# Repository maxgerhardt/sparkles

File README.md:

# Project sketch: whispering forest fireflies

### Motivation: 
Forests are amazing to illuminate but unfortunately most lighting art i have seen in the past years are immediately recognizable as LED strips. Also i’m looking for a technical challenge.

### Short description: 
build autonomous little waterproof devices that can be hung up in trees. They blink and have a speaker and can triangulate their relative position to each other by using sound. This way we can simply hang them up randomly and know where they are, running light and sound animations through a larger space. 

### How does this work? 
One base station knows its exact location and sends out a timestamp every second or so. During calibration we walk around the forest and produce loud noises, each individual device picks up those noises as peaks and calculates the time difference between the timestamp and the peak, thus collecting a table of runtimes. These runtimes are then sent to the base station and this way we can calculate each position with an accuracy of at least 30cm (which would be 1ms granularity for sound in air) or even quicker. We use ESP-NOW as wifi broadcast for the timestamp and additional commands. 

### How does the hardware look like? 
It’s going to be a custom pcb with a high power led on each side, an esp32, a cheap SMD microphone, a switch and some charging infrastructure, plus a loud speaker  You can plug in a lithium polymer battery and an esp8266 dev board to the pin headers. The whole thing needs to be encased in something waterproof but the idea is to smartly use the ESPs sleep functions to keep the whole thing running for the entire week and only work at night. 

### How do you want to charge 200 devices? 
Actually, we hope to get the battery and power consumption set up in a way that the devices can run for a whole week (power down during daylight etc), but the idea is also to have two notches in the width of a model railway track on the PCBs, so we can stick the boards on a long piece of track and charge all of them more or less at once. We might also do a sound installation during daytime and a light installation at night which creates even bigger need for charging infrastructure

### What challenges are there? 
Many. Getting the math of the audio triangulation right, actually doing some audio triangulation, getting an energy saving way of doing the wifi command stuff, possibly doing our own PWM on the LEDs instead of using WS2812 (e.g. to use brighter LEDs), getting some nice anmations running, also getting the sound animation right, getting all of this done in a cheap fashion etc etc. 

### Costs? 
The cheaper the unit the more we can make. I hope to get a unit including battery for under 10 euros and i hope to get a dream funded that allows us to get 200 units. The cool thing is that every year we could increase the amount of units to make the thing even more sparkly…

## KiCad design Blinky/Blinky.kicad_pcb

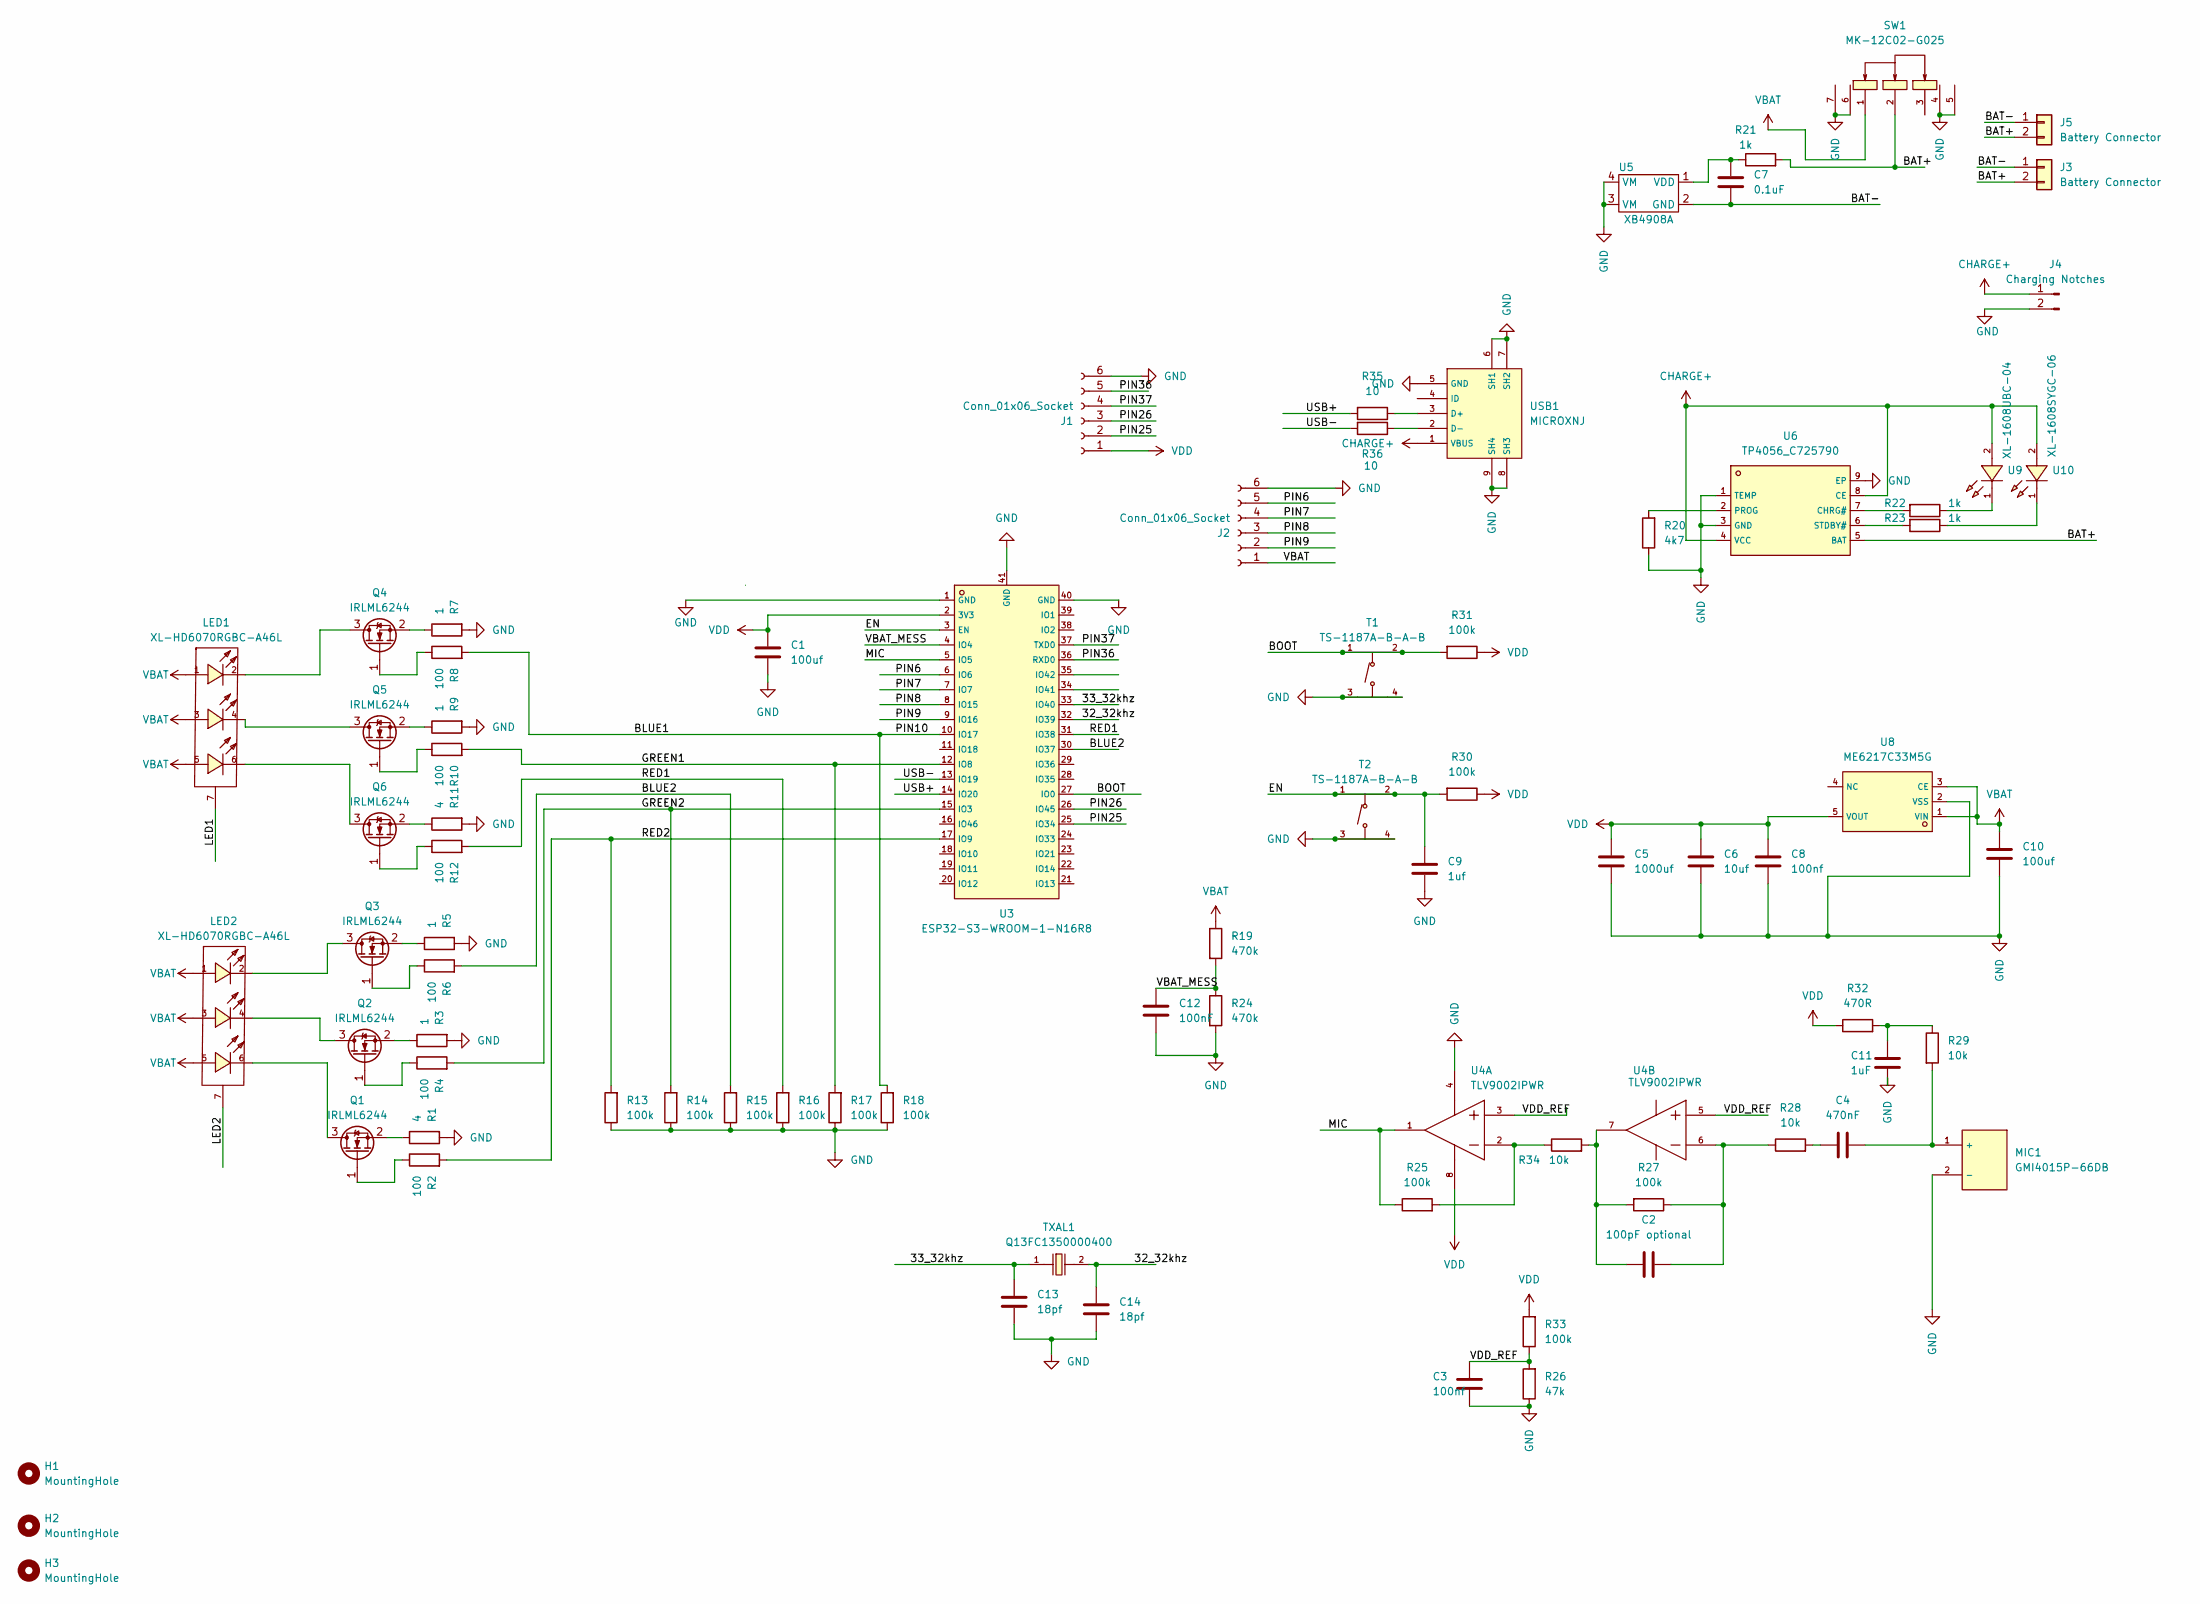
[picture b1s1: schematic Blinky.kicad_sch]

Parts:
C1, C10: 100uf; CASE-B_3528
C2: 100pF optional; C_0603_1608Metric
C3, C8: 100nf; C_0603_1608Metric
C4: 470nF; C_0603_1608Metric
C5: 1000uf; CAP-SMD_BD8.0-L8.3-W8.3-FD
C6: 10uf; C_0603_1608Metric
C7: 0.1uF; C_0603_1608Metric
C9: 1uf; C_0603_1608Metric
C11: 1uF; C_0603_1608Metric
C12: 100nF; C_0603_1608Metric
C13, C14: 18pf; C_0603_1608Metric
H1, H2, H3: MountingHole; MountingHole_3.2mm_M3
J1, J2: Conn_01x06_Socket; HDR-TH_6P-P2.54-V-F
J3, J5: Battery Connector; JST_PH_B2B-PH-K_1x02_P2.00mm_Vertical
J4: Charging Notches; ChargingNotches
LED1, LED2: XL-HD6070RGBC-A46L; LED-SMD_XL-HD6070RGBC-A46L; LCSC C5349977
MIC1: GMI4015P-66DB; MIC-TH_BD4.0-P1.4-D0.4-L-FD; LCSC C529912
Q1, Q2, Q3, Q4, Q5, Q6: IRLML6244; SOT-23
R1, R11: 4; R_0603_1608Metric
R2, R4, R6, R8, R10, R12: 100; R_0603_1608Metric
R3, R5, R7, R9: 1; R_0603_1608Metric
R13, R14, R15, R16, R17, R18, R25, R27, R30, R31, R33: 100k; R_0603_1608Metric
R19, R24: 470k; R_0603_1608Metric
R20: 4k7; R_0603_1608Metric
R21, R22, R23: 1k; R_0603_1608Metric
R26: 47k; R_0603_1608Metric
R28, R29, R34: 10k; R_0603_1608Metric
R32: 470R; R_0603_1608Metric
R35, R36: 10; R_0603_1608Metric
SW1: MK-12C02-G025; SW-SMD_MK-12C02-G025; LCSC C778186
T1, T2: TS-1187A-B-A-B; SW-SMD_4P-L5.1-W5.1-P3.70-LS6.5-TL-2; LCSC C318884
TXAL1: Q13FC1350000400; Crystal_SMD_3215-2Pin_3.2x1.5mm; LCSC C32346
U3: ESP32-S3-WROOM-1-N16R8; WIRELM-SMD_ESP32-S3-WROOM-1; LCSC C3040594
U4: TLV9002IPWR; TSSOP-8_L4.4-W3.0-P0.65-LS6.4-BL-2; LCSC C398359
U5: XB4908A
U6: TP4056_C725790; ESOP-8_L4.9-W3.9-P1.27-LS6.0-BL-EP; LCSC C725790
U8: ME6217C33M5G; SOT-23-5_L3.0-W1.7-P0.95-LS2.8-BR; LCSC C427602
U9: XL-1608UBC-04; LED0603-RD_BLUE; LCSC C965807
U10: XL-1608SYGC-06; LED0603-RD_GREEN; LCSC C965805
USB1: MICROXNJ; MICRO-USB-SMD_MICROXNJ; LCSC C404969

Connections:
/32_32khz: C14.1, TXAL1.2, U3.32 (IO39)
/33_32khz: C13.1, TXAL1.1, U3.33 (IO40)
/BAT+: J3.2, J5.2, R21.2, SW1.2, U6.5 (BAT)
/BAT-: C7.2, J3.1, J5.1, U5.2 (GND)
/BLUE1: R8.2, R18.2, U3.10 (IO17)
/BLUE2: R6.2, R15.2, U3.30 (IO37)
/BOOT: R31.2, T1.1 (A), T1.2 (B), U3.27 (IO0)
/EN: C9.2, R30.2, T2.1 (A), T2.2 (B), U3.3 (EN)
/GREEN1: R10.2, R17.2, U3.12 (IO8)
/GREEN2: R4.2, R14.2, U3.15 (IO3)
/LED1: LED1.7
/LED2: LED2.7
/MIC: R25.1, U3.5 (IO5), U4.1 (OUT1)
/PIN6: J2.5, U3.6 (IO6)
/PIN7: J2.4, U3.7 (IO7)
/PIN8: J2.3, U3.8 (IO15)
/PIN9: J2.2, U3.9 (IO16)
/PIN25: J1.2, U3.25 (IO34)
/PIN26: J1.3, U3.26 (IO45)
/PIN36: J1.5, U3.36 (RXD0)
/PIN37: J1.4, U3.37 (TXD0)
/RED1: R12.2, R16.2, U3.31 (IO38)
/RED2: R2.2, R13.2, U3.17 (IO9)
/USB+: R35.2, U3.14 (IO20)
/USB-: R36.2, U3.13 (IO19)
/VBAT_MESS: C12.2, R19.2, R24.1, U3.4 (IO4)
/VDD_REF: C3.1, R26.2, R33.1, U4.3 (IN1+), U4.5 (IN2+)
CHARGE+: J4.1, U6.4 (VCC), U6.8 (CE), U9.2 (A), U10.2 (A), USB1.1 (VBUS)
GND: C1.2, C3.2, C5.2, C6.1, C8.1, C9.1, C10.2, C11.2, C12.1, C13.2, C14.2, J1.6, J2.6, J4.2, MIC1.2 (-), R1.2, R3.2, R5.2, R7.2, R9.2, R11.2, R13.1, R14.1, R15.1, R16.1, R17.1, R18.1, R20.1, R24.2, R26.1, SW1.4, SW1.5, SW1.6, SW1.7, T1.3 (C), T1.4 (D), T2.3 (C), T2.4 (D), U3.1 (GND), U3.40 (GND), U3.41 (GND), U4.4 (V-), U5.3 (VM), U5.4 (VM), U6.1 (TEMP), U6.3 (GND), U6.9 (EP), U8.2 (VSS), USB1.5 (GND), USB1.6 (SH1), USB1.7 (SH2), USB1.8 (SH3), USB1.9 (SH4)
unnamed: C4.1, R28.2
unnamed: C11.1, R29.1, R32.2
unnamed: C4.2, MIC1.1 (+), R29.2
unnamed: LED2.6, Q1.3 (D)
unnamed: Q1.1 (G), R2.1
unnamed: Q1.2 (S), R1.1
unnamed: LED2.4, Q2.3 (D)
unnamed: Q2.1 (G), R4.1
unnamed: Q2.2 (S), R3.1
unnamed: LED2.2, Q3.3 (D)
unnamed: Q3.1 (G), R6.1
unnamed: Q3.2 (S), R5.1
unnamed: LED1.2, Q4.3 (D)
unnamed: Q4.1 (G), R8.1
unnamed: Q4.2 (S), R7.1
unnamed: LED1.4, Q5.3 (D)
unnamed: Q5.1 (G), R10.1
unnamed: Q5.2 (S), R9.1
unnamed: LED1.6, Q6.3 (D)
unnamed: Q6.1 (G), R12.1
unnamed: Q6.2 (S), R11.1
unnamed: R25.2, R34.1, U4.2 (IN1-)
unnamed: C2.2, R27.1, R28.1, U4.6 (IN2-)
unnamed: C2.1, R27.2, R34.2, U4.7 (OUT2)
unnamed: C7.1, R21.1, U5.1 (VDD)
unnamed: R22.2, U6.7 (CHRG#)
unnamed: R20.2, U6.2 (PROG)
unnamed: R23.2, U6.6 (STDBY#)
unnamed: R22.1, U9.1 (K)
unnamed: R23.1, U10.1 (K)
unnamed: R35.1, USB1.3 (D+)
unnamed: R36.1, USB1.2 (D-)
VBAT: C10.1, J2.1, LED1.1, LED1.3, LED1.5, LED2.1, LED2.3, LED2.5, R19.1, SW1.1, U8.1 (VIN), U8.3 (CE)
VDD: C1.1, C5.1, C6.2, C8.2, J1.1, R30.1, R31.1, R32.1, R33.2, U3.2 (3V3), U4.8 (V+), U8.5 (VOUT)

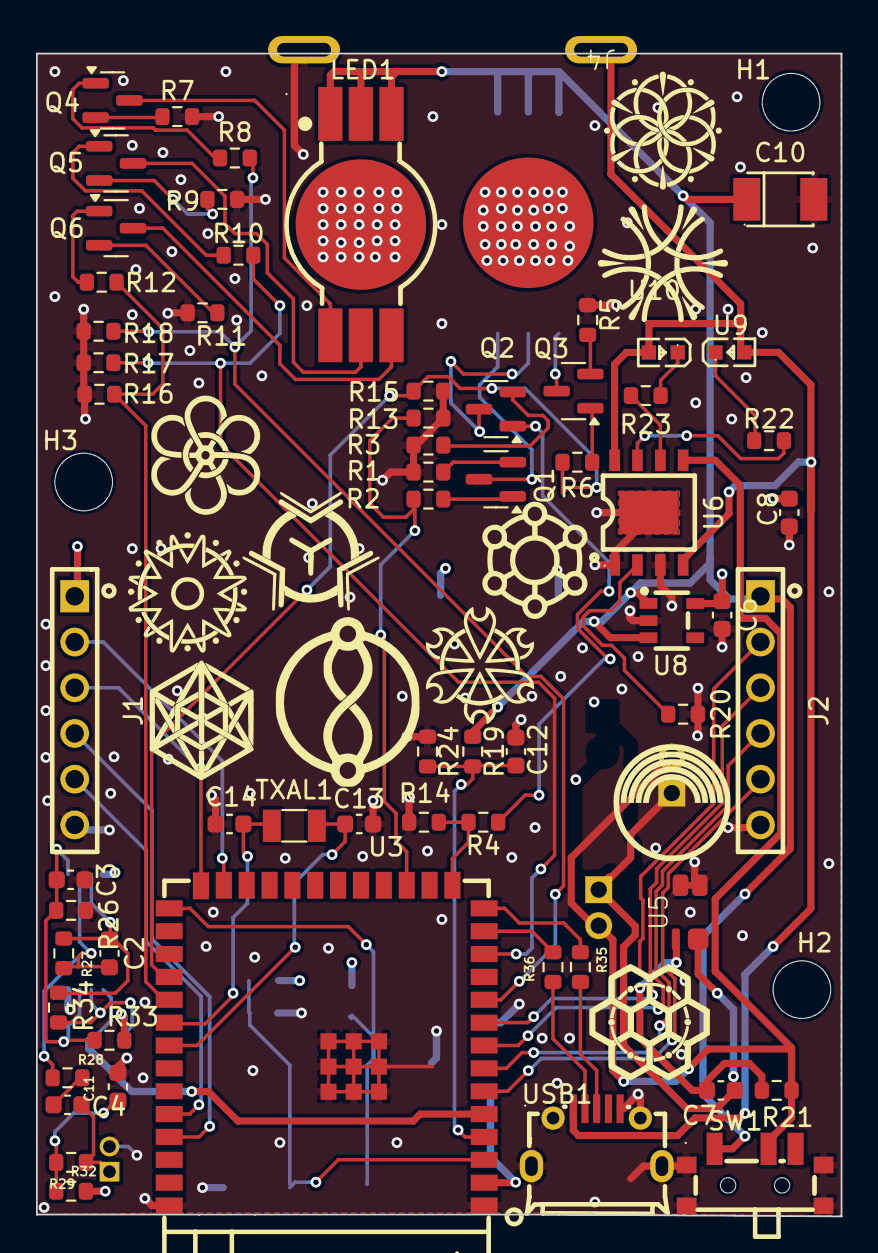
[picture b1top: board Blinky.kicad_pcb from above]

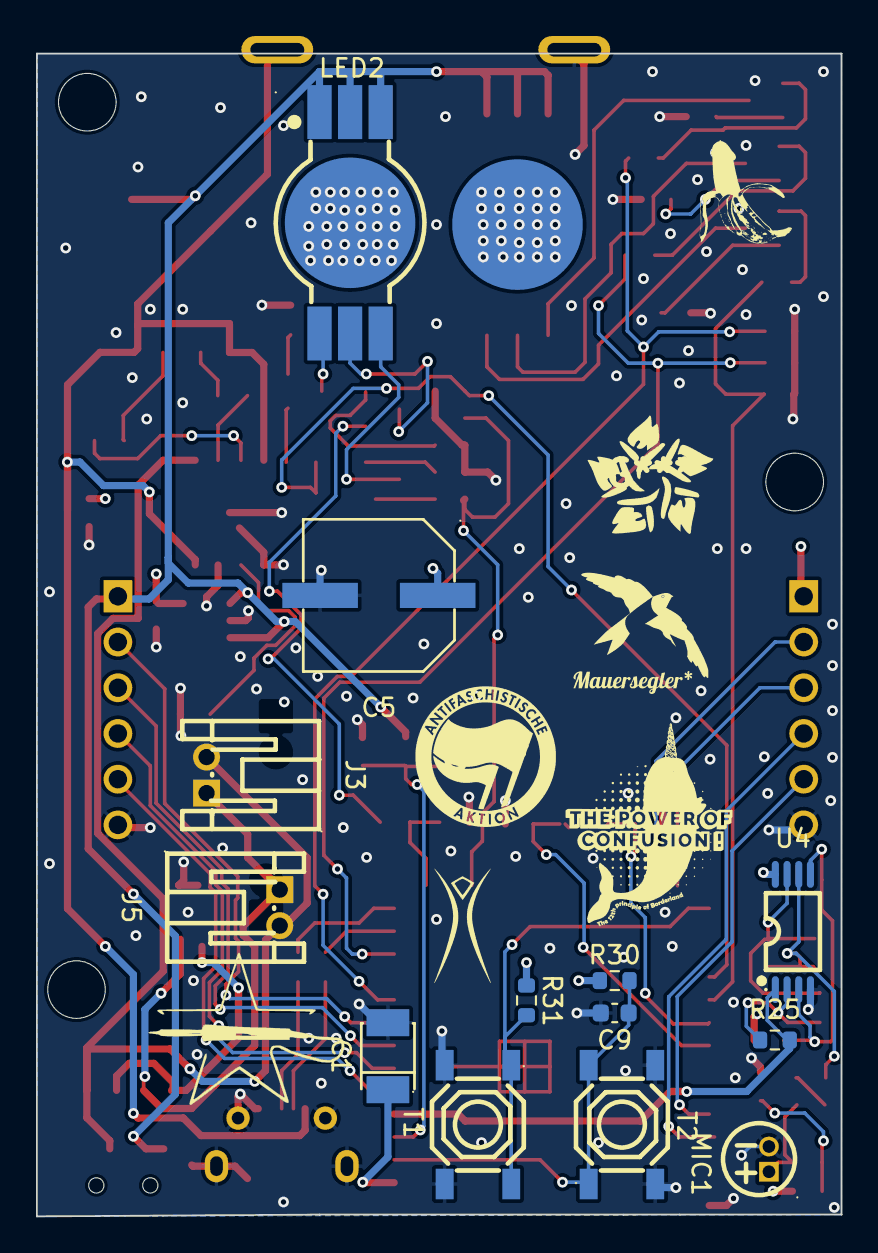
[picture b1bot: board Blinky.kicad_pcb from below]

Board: 4 copper layers, 44.7 x 64.6 mm, 80 parts (14 on the bottom side), 61 nets.

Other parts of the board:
LOGO102: Logo_Open_Hardware_Large; artwork

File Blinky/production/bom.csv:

Designator,Footprint,Quantity,Value,LCSC Part #
"C1, C10",CASE-B_3528,2,100uf,
"C11, C9",0603,2,1uF,
"C12, C3, C8",0603,3,100nF,
"C13, C14",0603,2,18pf,
C2,0603,1,100pF optional,
C4,0603,1,470nF,
C5,CAP-SMD_BD8.0-L8.3-W8.3-FD,1,1000uf,
C6,0603,1,10uf,
C7,0603,1,0.1uF,
"H1, H2, H3",MountingHole_3.2mm_M3,3,MountingHole,
"J1, J2",HDR-TH_6P-P2.54-V-F,2,Conn_01x06_Socket,
"J3, J5",JST_PH_B2B-PH-K_1x02_P2.00mm_Vertical,2,Battery Connector,
J4,ChargingNotches,1,Charging Notches,
"LED1, LED2",LED-SMD_XL-HD6070RGBC-A46L,2,XL-HD6070RGBC-A46L,C5349977
MIC1,MIC-TH_BD4.0-P1.4-D0.4-L-FD,1,GMI4015P-66DB,C529912
"Q1, Q2, Q3, Q4, Q5, Q6",SOT-23,6,IRLML6244,
"R1, R11",0603,2,4,
"R10, R12, R2, R4, R6, R8",0603,6,100,
"R13, R14, R15, R16, R17, R18, R25, R27, R30, R31, R33",0603,11,100k,
"R19, R24",0603,2,470k,
R20,0603,1,4k7,
"R21, R22, R23",0603,3,1k,
R26,0603,1,47k,
"R28, R29, R34",0603,3,10k,
"R3, R5, R7, R9",0603,4,1,
R32,0603,1,470R,
"R35, R36",0603,2,10,
SW1,SW-SMD_MK-12C02-G025,1,MK-12C02-G025,C778186
"T1, T2",SW-SMD_4P-L5.1-W5.1-P3.70-LS6.5-TL-2,2,TS-1187A-B-A-B,C318884
TXAL1,Crystal_SMD_3215-2Pin_3.2x1.5mm,1,Q13FC1350000400,C32346
U10,LED0603-RD_GREEN,1,XL-1608SYGC-06,C965805
U3,WIRELM-SMD_ESP32-S3-WROOM-1,1, ESP32-S3-WROOM-1-N16R8,C3040594
U4,TSSOP-8_L4.4-W3.0-P0.65-LS6.4-BL-2,1,TLV9002IPWR,C398359
U5,XB4908A,1,XB4908A,
U6,ESOP-8_L4.9-W3.9-P1.27-LS6.0-BL-EP,1,TP4056_C725790,C725790
U8,SOT-23-5_L3.0-W1.7-P0.95-LS2.8-BR,1,ME6217C33M5G,C427602
U9,LED0603-RD_BLUE,1,XL-1608UBC-04,C965807
USB1,MICRO-USB-SMD_MICROXNJ,1,MICROXNJ,C404969

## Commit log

2023-08-25 Added Calibration Points Generator
2023-08-28 added main config arduino project
2023-08-28 Added client config arduino project
2023-08-28 whatever
2023-08-28 done
2023-08-28 added modes v1
2023-08-29 added a bunch of messaging. good night checkin.
2023-08-29 address exchange
2023-08-29 test
2023-08-30 inbetween / next up rewrite for esp32
2023-09-01 debug
2023-09-02 sending messages and measuring latencies
2023-09-05 Message State Machine.drawio
2023-09-05 updated messaging and added doc
2023-09-06 added multiple message modes
2023-09-06 pre debug all done except for location calculation and sending
2023-09-07 cleaned up a little
2023-09-07 cleaned up
2023-09-11 improved messaging
2023-09-13 moved documentation.md
2023-09-26 Added Schematic
2023-09-26 bugfix
2023-09-29 beta schematic
2023-10-03 updated Schematic
2023-10-10 updated pcb layout
2023-10-12 updated pcb
2023-11-22 ordered prototype
2023-12-15 newest version
2024-01-28 did some stuff
2024-01-31 zwischenstand
2024-02-19 parts
2024-02-19 version 1.9
2024-02-19 version 1.95
2024-02-19 removed gnd from back of led
2024-02-19 connected pin headers to GPIOs
2024-02-19 removed ground connection for LED backside, added flipside led copper
2024-02-23 switched around resistors for LEDs
2024-02-23 doubled resistor values for LEDs
2024-02-23 added C after voltage reg
2024-02-25 fixed Vreg and Mic
2024-02-25 fixed routing of u8 pin 3
2024-02-25 cosmetics
2024-02-27 trying to fix C5
2024-02-27 reordered
2024-02-28 reordered and fixed stuff
2024-02-28 removed some violations
2024-03-03 review by blueloop
2024-03-15 3d work and fixed 90 deg rotation in capacitor issue
2024-03-15 old revision in client
2024-03-23 branch commit
2024-03-30 timer works, needs animation
2024-03-31 synchronous flashing
2024-04-03 synchronous blink works
2024-04-09 casing update
2024-04-09 candle on device 9
2024-04-11 casing almost done
2024-04-11 switching to main
2024-04-11 updated casing
2024-04-11 zwischnstand
2024-04-11 copying over
2024-04-12 bottom cutout width
2024-04-12 fixed casing
2024-04-14 board v3 0.8
2024-04-15 updated board
2024-04-15 messaging
2024-04-15 showing martin stuff
2024-04-16 moved stuff
2024-04-17 redefiniton
2024-04-17 showing martin
2024-04-17 testing something
2024-04-17 for martin
2024-04-18 new Board
2024-04-18 weirdness galore
2024-04-19 fuer alex
2024-04-20 weird bug
2024-04-22 consolidating
2024-04-23 updated a few things
2024-04-24 webserver stuff
2024-04-26 fuer markus
2024-04-28 Delete Blinky/_autosave-Blinky.kicad_pcb
    deleted autosaves
2024-04-28 C1 größerer Footprint Layout angepasst, geprüft Fehlende Footprints ergänzt.
2024-04-28 in between
2024-05-06 added clapping
2024-05-08 Count distances
2024-05-08 little fix
2024-05-13 can't find this fuckign error
2024-05-23 hardware check
2024-05-26 fixed final
2024-05-26 fixed reverse battery connectors
2024-06-15 animation plus timesync
2024-06-19 zwischen
2024-06-19 Fixup compilation
2024-06-19 Add CI
